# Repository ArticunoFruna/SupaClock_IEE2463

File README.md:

# SupaClock — Contexto y Guía del Proyecto

SupaClock es un sistema de salud inteligente usable (*wearable*) de pulsera desarrollado como parte del curso IEE2463. Su propósito es capturar biometría crítica en tiempo real, procesarla tanto en el dispositivo mediante técnicas de Inteligencia Artificial en el borde (TinyML), enviarla vía Bluetooth Low Energy (BLE) a una aplicación móvil de compañía y respaldarla de forma segura en la nube.

Este documento consolida el contexto general, características, funcionamiento de los sensores, arquitectura técnica y la organización del código según las tareas de desarrollo del proyecto.

---

## 1. Características Principales

*   **Procesamiento Concurrente y Multitarea:** Implementado bajo **ESP-IDF** (entorno oficial de Espressif) corriendo sobre **FreeRTOS** en un microcontrolador **Seeed Studio XIAO ESP32-S3** (y soportando el módulo **ESP32-C3 SuperMini** para captura de datos). Esto permite dividir el firmware en tareas con prioridades asignadas (adquisición de alta prioridad, procesamiento de actividad, interfaz gráfica e hilos de comunicación BLE).
*   **TinyML (Human Activity Recognition - HAR) en el Borde:** Inferencia en tiempo real de actividades físicas (Reposo, Caminar, Correr) ejecutada directamente en el reloj con un modelo de red neuronal convolucional 1D (CNN 1D) optimizado e integrado en C puro (`har_cnn1d`), operando con un muestreo del acelerómetro a 50 Hz.
*   **Interfaz Gráfica Integrada:** Pantalla LCD a color manejada mediante la librería gráfica **LVGL v8.4**, con refresco optimizado utilizando el bus SPI y **DMA (Direct Memory Access)** para liberar ciclos de procesamiento de la CPU.
*   **Aplicación Móvil Multiplataforma (Flutter & Dart):** 
    *   **Vista de Usuario:** Tablero interactivo con métricas en tiempo real, historial médico local e inicio de mediciones puntuales (*spot-checks*).
    *   **Procesamiento de Señales Local:** Incorpora el algoritmo **Pan-Tompkins** directamente en Dart para la detección de picos QRS y análisis de variabilidad del ritmo cardíaco (HRV) a partir de lecturas de ECG sin necesidad de servidores.
    *   **Modo Clínico:** Umbrales biométricos personalizables con lógica de estabilidad temporal para evitar falsas alarmas que disparan notificaciones locales y registros en la base de datos.
    *   **Modo Desarrollador Oculto:** Desbloqueado presionando 7 veces la versión en la pantalla de Configuración, otorgando acceso a flujos crudos de señales (ECG/IMU), grabación local a CSV e interfaz de comandos directos.
*   **Almacenamiento Local-First y Nube Serverless:** Almacenamiento local mediante Hive y sincronización asíncrona hacia Google Firebase (**Firestore** para métricas y **Storage** para las grabaciones CSV de electrocardiogramas completos), minimizando costes de infraestructura al no depender de Cloud Functions.

---

## 2. Sensores y Método de Funcionamiento

El dispositivo integra múltiples sensores biométricos conectados al bus físico común del microcontrolador.

### Resumen de Sensores
1.  **BMI160 (IMU - Unidad de Medición Inercial):** Acelerómetro y giroscopio conectados a través del bus **I2C**. Captura movimientos a 50 Hz para el algoritmo del podómetro (conteo de pasos) y para alimentar el modelo HAR en el borde.
2.  **AD8232 (ECG - Electrocardiograma):** Sensor analógico de pulso cardíaco de un solo canal. Se lee mediante el **ADC** interno del ESP32 a una frecuencia de muestreo de 500 Hz. Permite la visualización de la onda del electrocardiograma y el cálculo de intervalos RR.
3.  **MAX30102 (Pulsioxímetro):** Sensor óptico de ritmo cardíaco y saturación de oxígeno en sangre (SpO₂). Se comunica por **I2C**.
4.  **MAX30205 (Termómetro Clínico):** Sensor de temperatura de alta precisión diseñado para monitorización corporal humana. Se comunica por **I2C**.
5.  **MAX17048 (Fuel Gauge - Medidor de Batería):** Monitorea el voltaje y estado de carga de la batería Li-Po a través del bus **I2C**.

### Interfaz Física y buses de Comunicación
*   **Bus I2C (Compartido):** Los sensores BMI160, MAX30102, MAX30205 y MAX17048 comparten las líneas SDA y SCL del microcontrolador. Cada uno se identifica por su dirección de hardware hexadecimal única. Para evitar conflictos entre tareas concurrentes que acceden a este bus, el firmware emplea **Mutexes** de exclusión mutua de FreeRTOS.
*   **Bus SPI (Dedicado):** La pantalla LCD **ST7789** utiliza el bus SPI a alta velocidad con DMA para transferir buffers completos de píxeles generados en memoria RAM por LVGL.

### Protocolo de Comunicación BLE
El reloj actúa como servidor GATT y expone cuatro características principales bajo el protocolo biométrico de SupaClock:

| Característica UUID | Dirección | Descripción / Estructura del Dato |
| :--- | :--- | :--- |
| **`0xFF01`** | Notificación | **Flujo IMU Crudo:** Envío continuo a 50 Hz de paquetes de 12 bytes (`int16 ax, ay, az, gx, gy, gz`). |
| **`0xFF02`** | Notificación | **Métricas Agregadas (TLV):** Paquetes estructurados que contienen un encabezado y registros *Type-Length-Value* de variables (Ritmo cardíaco, SpO₂, Temperatura, Pasos, Batería, Estado HAR). |
| **`0xFF03`** | Notificación | **Flujo ECG Crudo:** Envío a 500 Hz de paquetes de 20 bytes que empaquetan 10 muestras consecutivas de ECG (`int16`). |
| **`0xFF04`** | Escritura | **Consola de Comandos:** Envío de órdenes al reloj (`0x00` detiene ECG, `0x01` inicia ECG, `0x02` activa depuración HAR, `0x03` detiene depuración). |

El formato **TLV (Type-Length-Value)** de la característica `0xFF02` estructura la información de la siguiente manera:
*   **Cabecera:** `Timestamp (u32)` + `Modo Energía (u8)` + `Longitud Datos (u8)`.
*   **Tipos de Registro (Types):**
    *   `0x01`: Frecuencia Cardíaca (BPM y calidad de señal).
    *   `0x02`: Saturación de Oxígeno (SpO₂ y calidad de señal).
    *   `0x03`: Temperatura Corporal.
    *   `0x04`: Estado de la Batería.
    *   `0x05`: Conteo de Pasos.
    *   `0x08`: Estado de Actividad HAR Consolidado.

---

## 3. Estructura de Directorios y Tareas de Desarrollo

El código fuente del proyecto se encuentra estructurado en carpetas dedicadas según el área de ingeniería y desarrollo:

```
SupaClock_IEE2463/
├── app/                  # Aplicación móvil en Flutter (Frontend y lógica del teléfono)
├── src/                  # Entrypoint del firmware y pruebas en ESP-IDF
├── lib/                  # Librerías internas y drivers de hardware para PlatformIO
├── hardware/             # Esquemáticos y PCB (diseño electrónico en Eagle/Kicad)
├── mechanical/           # Modelado en 3D del chasis y botón del reloj (OpenSCAD/STL)
├── tools/                # Scripts de Python para entrenamiento, simulaciones y debug
├── data_ml/              # Base de datos local de acelerometría para entrenamiento HAR
├── docs/                 # Hojas de datos (Datasheets), especificaciones y entregables
├── pc_simulator/         # Simulador de la interfaz gráfica en PC
└── scripts/              # Herramientas auxiliares y de generación de recursos gráficos
```

### 📂 Distribución de Tareas y Directorios de Trabajo

#### 1. Tareas de Firmware (C y C++ sobre ESP-IDF / FreeRTOS)
*   **Directorio principal de código:** [src/](file:///home/jay-c/Desktop/SupaClock_IEE2463/src) y [lib/](file:///home/jay-c/Desktop/SupaClock_IEE2463/lib)
*   **Configuración del entorno:** [platformio.ini](file:///home/jay-c/Desktop/SupaClock_IEE2463/platformio.ini) define los parámetros de compilación y dependencias.
*   **Controladores de sensores:** Ubicados en `lib/` bajo los nombres de cada driver:
    *   `bmi160_driver/` (Acelerómetro/Giroscopio)
    *   `max30102_driver/` (Pulsioximetría)
    *   `max30205_driver/` (Temperatura)
    *   `max17048_driver/` (Batería)
    *   `ad8232_driver/` & `ad8232_c3_driver/` (Electrocardiografía)
*   **Motor Gráfico (LVGL) y UI del Reloj:** Se trabaja en [lib/supaclock_ui/](file:///home/jay-c/Desktop/SupaClock_IEE2463/lib/supaclock_ui), [lib/ui_theme/](file:///home/jay-c/Desktop/SupaClock_IEE2463/lib/ui_theme) y [lib/ui_fonts/](file:///home/jay-c/Desktop/SupaClock_IEE2463/lib/ui_fonts).
*   **TinyML (CNN 1D) e Inferencia:** La lógica de red neuronal se encuentra en [lib/har_cnn1d/](file:///home/jay-c/Desktop/SupaClock_IEE2463/lib/har_cnn1d).
*   **Infraestructura BLE:** Las definiciones del protocolo e hilos de transmisión están en [lib/ble_telemetry/](file:///home/jay-c/Desktop/SupaClock_IEE2463/lib/ble_telemetry).
*   **Pruebas de Componentes:** Código para validar hardware de forma aislada en [src/tests/](file:///home/jay-c/Desktop/SupaClock_IEE2463/src/tests) (por ejemplo, tests de pantalla, BLE, sensores específicos o algoritmos particulares).

#### 2. Tareas de Desarrollo Móvil (Flutter & Dart)
*   **Directorio de trabajo:** [app/](file:///home/jay-c/Desktop/SupaClock_IEE2463/app)
*   **Interfaz de Usuario:** Vistas e interfaces en [app/lib/screens/](file:///home/jay-c/Desktop/SupaClock_IEE2463/app/lib/screens) (dashboard, settings, spot-check, dev-mode).
*   **Persistencia Local y Backend (Firebase):** Configuración de bases de datos y sincronización en [app/lib/services/](file:///home/jay-c/Desktop/SupaClock_IEE2463/app/lib/services) (`firestore_service.dart`, `storage_service.dart`, `local_store.dart` usando Hive).
*   **Procesamiento de Señal (ECG) y BLE:** Algoritmo Pan-Tompkins en `app/lib/services/pan_tompkins.dart` y parseo de tramas de telemetría en `app/lib/services/ble_service.dart`.
*   **Modelos de Datos:** Declarados en [app/lib/models/](file:///home/jay-c/Desktop/SupaClock_IEE2463/app/lib/models) para asegurar concordancia con Firebase.

#### 3. Tareas de Machine Learning y Análisis Científico (Python)
*   **Entrenamiento y Reentrenamiento HAR:** Los scripts para construir el modelo de actividad física se encuentran en [tools/train_har_cnn.py](file:///home/jay-c/Desktop/SupaClock_IEE2463/tools/train_har_cnn.py) y [tools/train_har_cnn_c3.py](file:///home/jay-c/Desktop/SupaClock_IEE2463/tools/train_har_cnn_c3.py).
*   **Recopilación de Datasets:** El historial de datasets recopilados clasificados para entrenar el clasificador se trabaja en [data_ml/](file:///home/jay-c/Desktop/SupaClock_IEE2463/data_ml) (ej. resting, walking, running, stairs).
*   **Reproducción y Debug del Modelo (Replay):** Script [tools/har_replay.py](file:///home/jay-c/Desktop/SupaClock_IEE2463/tools/har_replay.py) corre el modelo `.tflite` sobre logs de acelerometría y simula los filtros de suavizado.
*   **Calibración y Simulación de Umbrales:** `tools/calibrate_steps.py` (conteo de pasos) y `tools/debug_pt.py` (simulador Pan-Tompkins).
*   **Monitoreo del Hardware:** [tools/supaclock_monitor.py](file:///home/jay-c/Desktop/SupaClock_IEE2463/tools/supaclock_monitor.py) es una aplicación de escritorio para graficar ondas IMU/ECG y enviar comandos por puerto serie/BLE.

#### 4. Tareas de Diseño de Hardware (Electrónica / PCB)
*   **Directorio de trabajo:** [hardware/](file:///home/jay-c/Desktop/SupaClock_IEE2463/hardware)
*   Contiene los esquemáticos y placas (`.sch` y `.brd`) para el circuito portador del reloj, el módulo ECG AD8232 y el módulo medidor de batería, además de scripts de soporte de conexión como `build_v4_schematics.py` o `dump_nets.py`.

#### 5. Tareas de Diseño Mecánico (Carcasa y Botones)
*   **Directorio de trabajo:** [mechanical/](file:///home/jay-c/Desktop/SupaClock_IEE2463/mechanical)
*   Lugar donde se diseñan las cubiertas (superior, inferior y botones) en OpenSCAD (`.scad`) y se exportan a STL para manufactura mediante impresión 3D (`mechanical/stl/`, `mechanical/stl_v3/`).

#### 6. Tareas de Documentación del Proyecto
*   **Directorio de trabajo:** [docs/](file:///home/jay-c/Desktop/SupaClock_IEE2463/docs)
*   Incluye los manuales de arquitectura y conceptos (`docs/arquitectura_conceptos.md`), guías para nuevos desarrolladores (`docs/guia_introductoria.md`), protocolos de comunicación (`docs/ble_har_protocol.md`), resúmenes de avances e informes para las evaluaciones académicas del curso (`docs/Entrega1` a `docs/Entrega4`).

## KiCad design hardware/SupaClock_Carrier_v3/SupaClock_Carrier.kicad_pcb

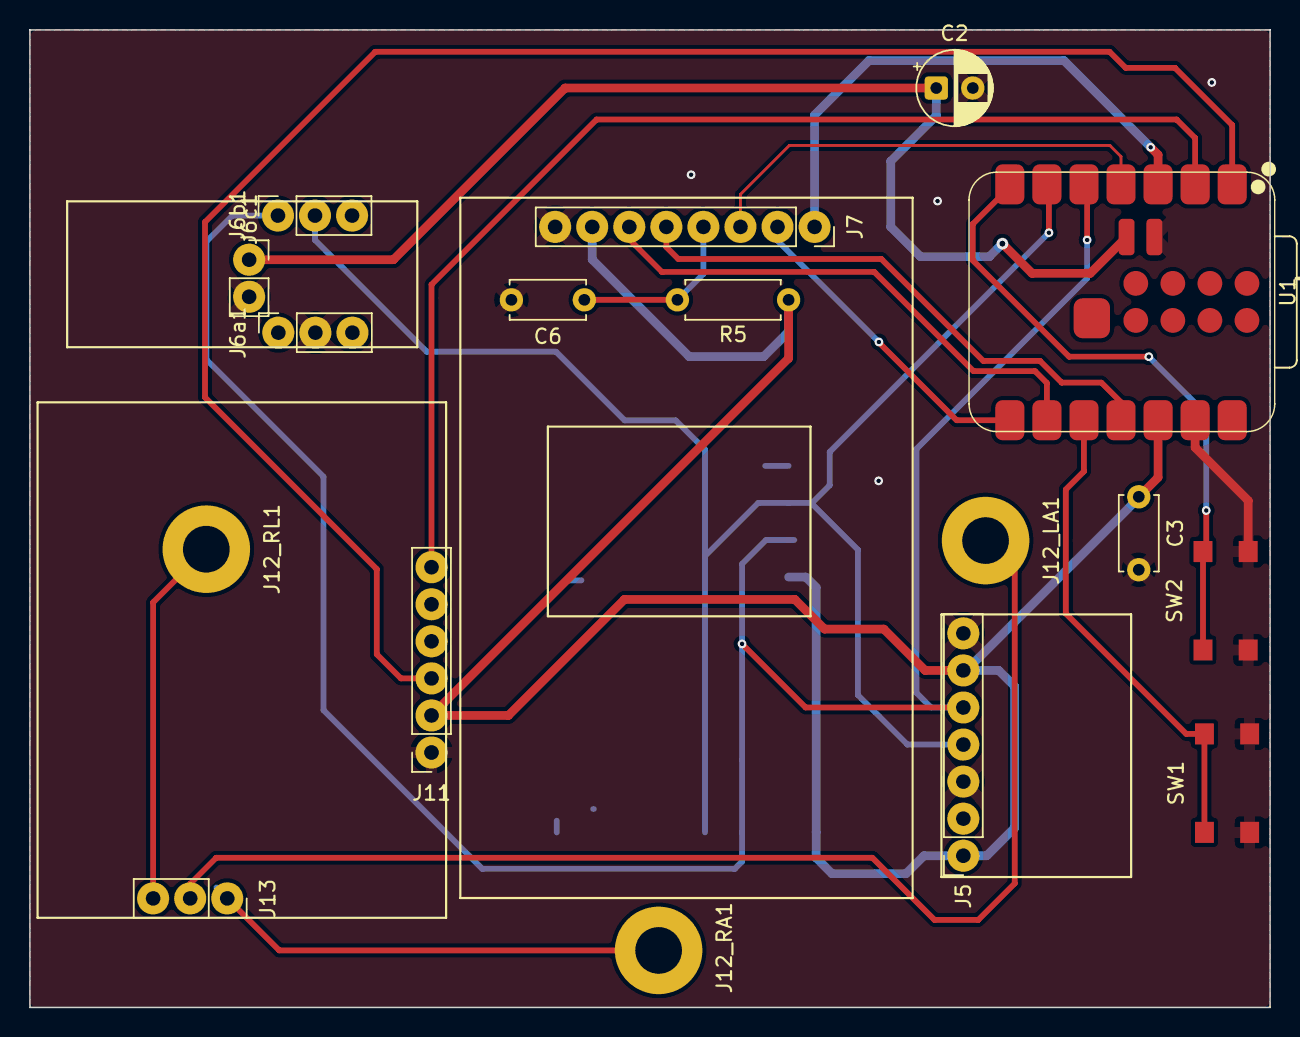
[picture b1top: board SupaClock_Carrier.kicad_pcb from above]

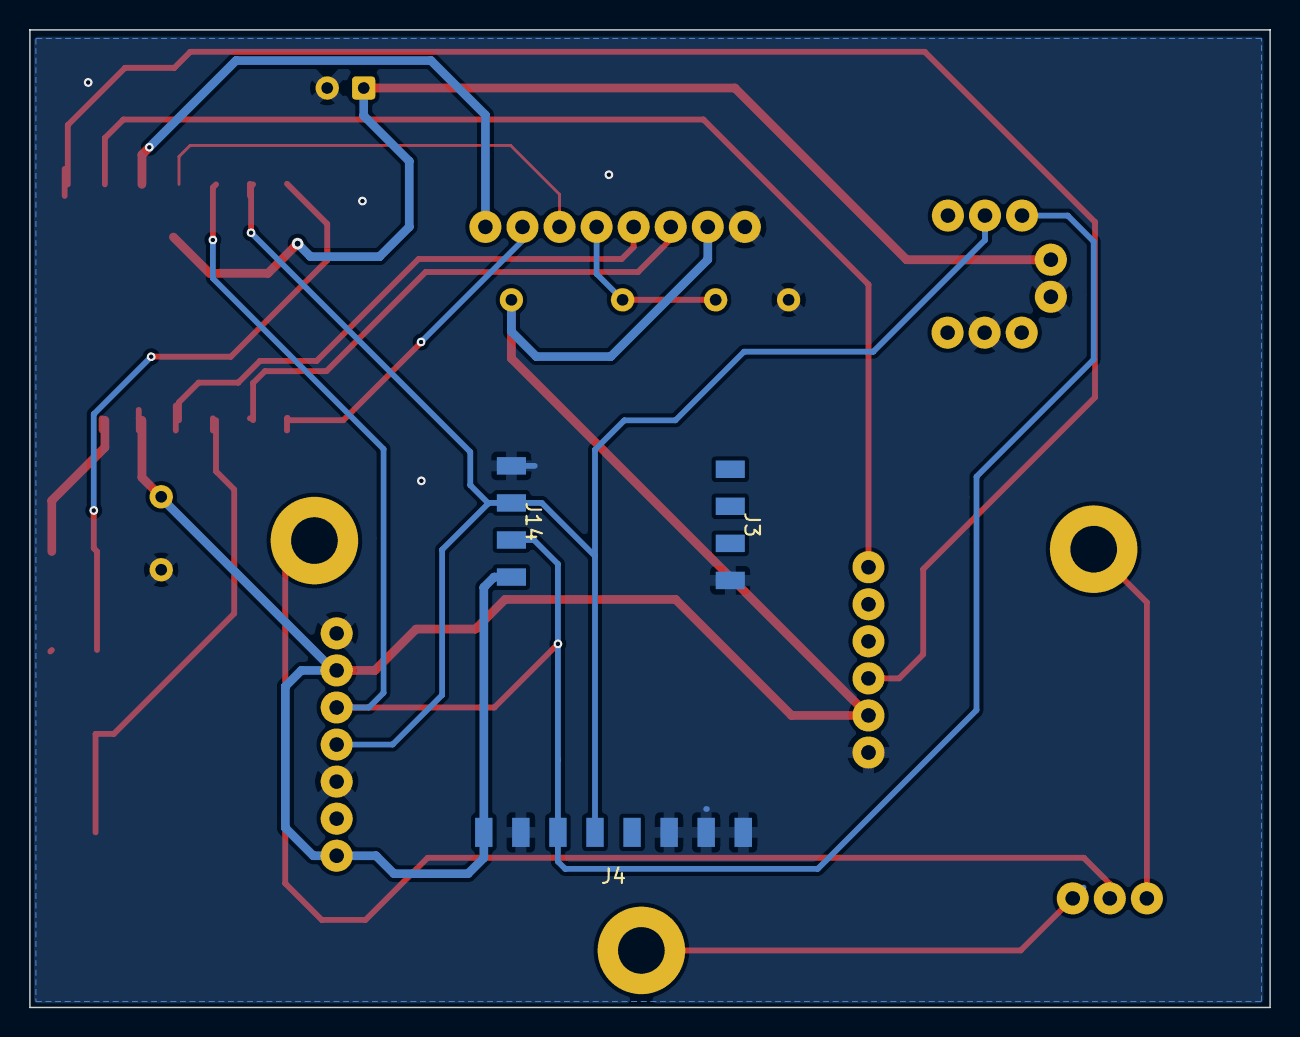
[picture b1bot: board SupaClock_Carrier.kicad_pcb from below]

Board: 2 copper layers, 85.0 x 67.0 mm, 20 parts (3 on the bottom side), 18 nets.

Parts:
C2: 10uF; CP_Radial_D5.0mm_P2.50mm
C3, C6: 100nF; C_Disc_D5.0mm_W2.5mm_P5.00mm
J3: MAX30102_top; MAX30102_Castellated_1x4
J4: MAX30205_8pad; MAX30205_8pad_Flush
J5: BMI160_7p; PinSocket_1x07_P2.54mm_Vertical
J6a1: MAX17048_L; PinSocket_1x03_P2.54mm_Vertical
J6b1: MAX17048_R; PinSocket_1x03_P2.54mm_Vertical
J6c1: MAX17048_BAT; PinSocket_1x02_P2.54mm_Vertical
J7: ST7789_1.69in; PinSocket_1x08_P2.54mm_Vertical
J11: AD8232_SparkFun; PinSocket_1x06_P2.54mm_Vertical
J12_LA1: ECG_LA_pad_M3; M3_Electrode_Pad
J12_RA1: ECG_RA_pad_M3; M3_Electrode_Pad
J12_RL1: ECG_RL_pad_M3; M3_Electrode_Pad
J13: AD8232_Pads_RA_LA_RL; PinSocket_1x03_P2.54mm_Vertical
J14: MAX30102_bot; MAX30102_Castellated_1x4
R5: 10k; R_Axial_DIN0207_L6.3mm_D2.5mm_P7.62mm_Horizontal
SW1: SELECT; SW_Tactile_Side_3.5x7.8mm
SW2: NEXT; SW_Tactile_Side_3.5x7.8mm
U1: XIAO-ESP32-S3; XIAO-ESP32-S3-SMD

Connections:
/+3V3: C3.1, J4.1, J5.1, J5.6, J7.7, J11.2, J14.1, R5.1, U1.12 (3V3)
/+BATT: C2.1, J6c1.1, U1.32 (BAT)
/BLK_PWM: J7.1, U1.3 (GPIO3_A2_D2)
/BTN_NEXT: SW2.1, U1.7 (GPIO43_D6_TX)
/BTN_SELECT: SW1.1, U1.10 (GPIO8_A9_D9_MISO)
/ECG_LA: J12_LA1.1 (Pin_1_1), J13.2
/ECG_OUT: J11.3, U1.1 (GPIO1_A0_D0)
/ECG_RA: J12_RA1.1 (Pin_1_1), J13.1
/ECG_RL: J12_RL1.1 (Pin_1_1), J13.3
/ECG_SDN: J11.6, U1.2 (GPIO2_A1_D1)
/GND: C2.2, C3.2, C6.2, J3.1 (Pin_1_1), J4.2, J4.6, J4.7, J4.8, J5.3, J5.7, J6a1.2 (Pin_2_2), J6c1.2, J7.8, J11.1, J14.4, SW1.2, SW2.2, U1.13 (GND), U1.33 (GND)
/I2C_SCL: J4.4, J5.4, J6b1.2, J14.3, U1.6 (GPIO6_A5_D5_SCL)
/I2C_SDA: J4.3, J5.5, J6b1.1, J14.2, U1.5 (GPIO5_A4_D4_SDA)
/SPI_CS: J7.2, U1.8 (GPIO44_D7_RX)
/SPI_DC: J7.3, U1.4 (GPIO4_A3_D3)
/SPI_MOSI: J7.5, U1.11 (GPIO9_A10_D10_MOSI)
/SPI_RES: C6.1, J7.4, R5.2
/SPI_SCK: J7.6, U1.9 (GPIO7_A8_D8_SCK)

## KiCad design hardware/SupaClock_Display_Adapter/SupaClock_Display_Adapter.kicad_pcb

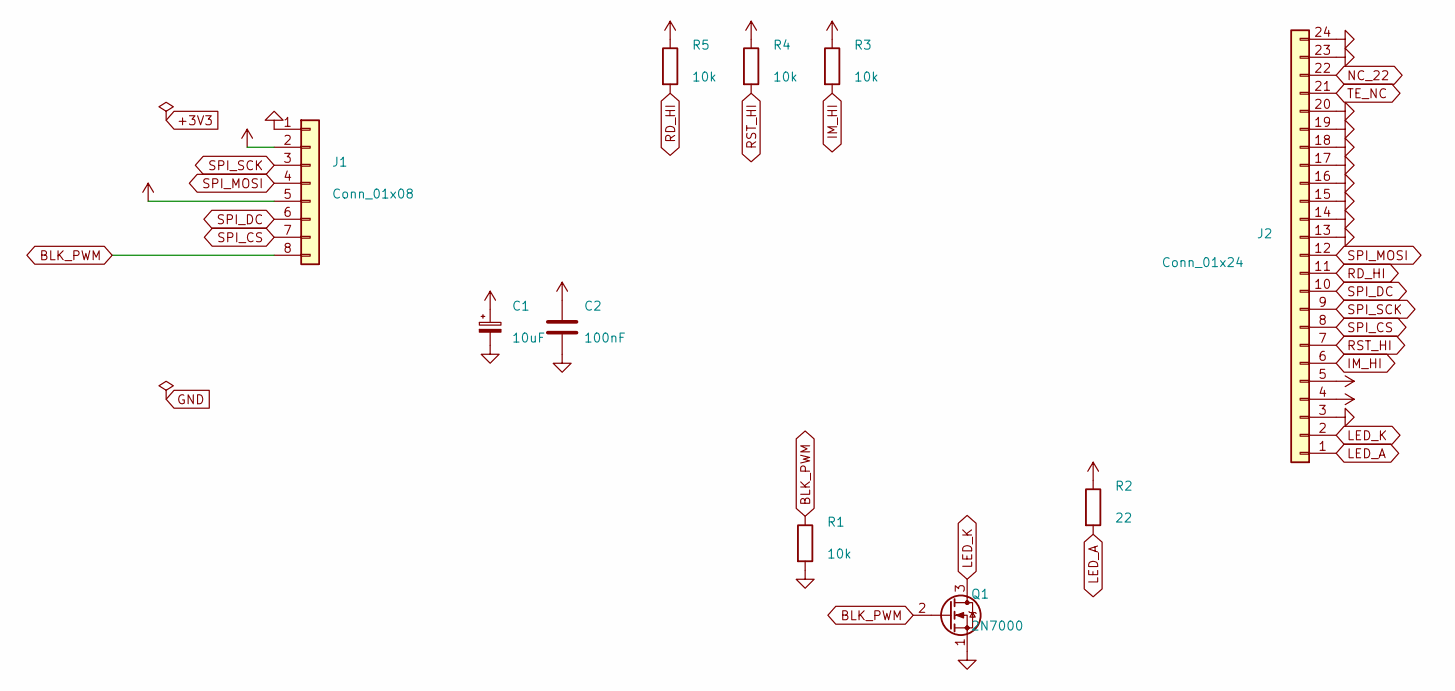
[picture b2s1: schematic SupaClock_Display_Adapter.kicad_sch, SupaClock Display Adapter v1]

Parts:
C1: 10uF; CP_Radial_D5.0mm_P2.50mm
C2: 100nF; C_Disc_D3.0mm_W1.6mm_P2.50mm
J1: Conn_01x08; PinHeader_1x08_P2.54mm_Vertical
J2: Conn_01x24; Hirose_FH12-24S-0.5SH_1x24-1MP_P0.50mm_Horizontal
Q1: 2N7000; TO-92_Inline
R1, R3, R4, R5: 10k; R_Axial_DIN0207_L6.3mm_D2.5mm_P10.16mm_Horizontal
R2: 22; R_Axial_DIN0207_L6.3mm_D2.5mm_P10.16mm_Horizontal

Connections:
+3V3: C1.1, C2.1, J1.2, J1.5, J2.4, J2.5, R2.1, R3.1, R4.1, R5.1
BLK_PWM: J1.8, Q1.2 (G), R1.1
GND: C1.2, C2.2, J1.1, J2.3, J2.13, J2.14, J2.15, J2.16, J2.17, J2.18, J2.19, J2.20, J2.23, J2.24, Q1.1 (S), R1.2
IM_HI: J2.6, R3.2
LED_A: J2.1, R2.2
LED_K: J2.2, Q1.3 (D)
NC_22: J2.22
RD_HI: J2.11, R5.2
RST_HI: J2.7, R4.2
SPI_CS: J1.7, J2.8
SPI_DC: J1.6, J2.10
SPI_MOSI: J1.4, J2.12
SPI_SCK: J1.3, J2.9
TE_NC: J2.21

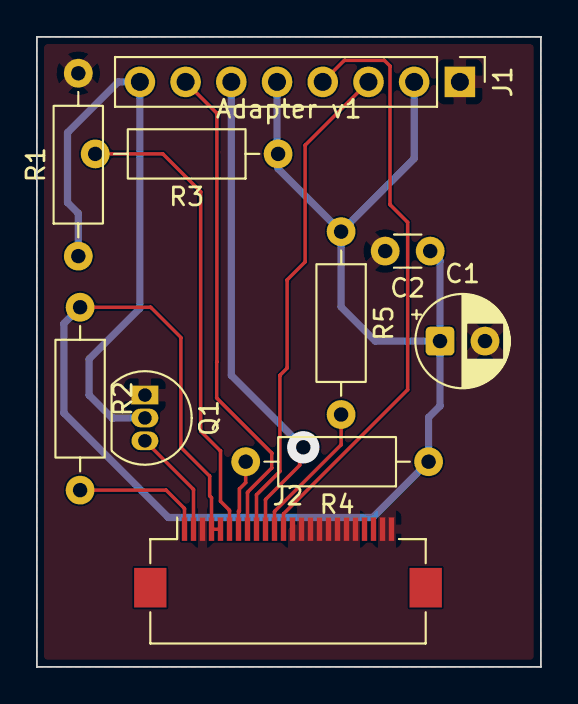
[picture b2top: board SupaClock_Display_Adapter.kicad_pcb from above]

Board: 2 copper layers, 28.0 x 35.0 mm, 10 parts (0 on the bottom side), 12 nets.

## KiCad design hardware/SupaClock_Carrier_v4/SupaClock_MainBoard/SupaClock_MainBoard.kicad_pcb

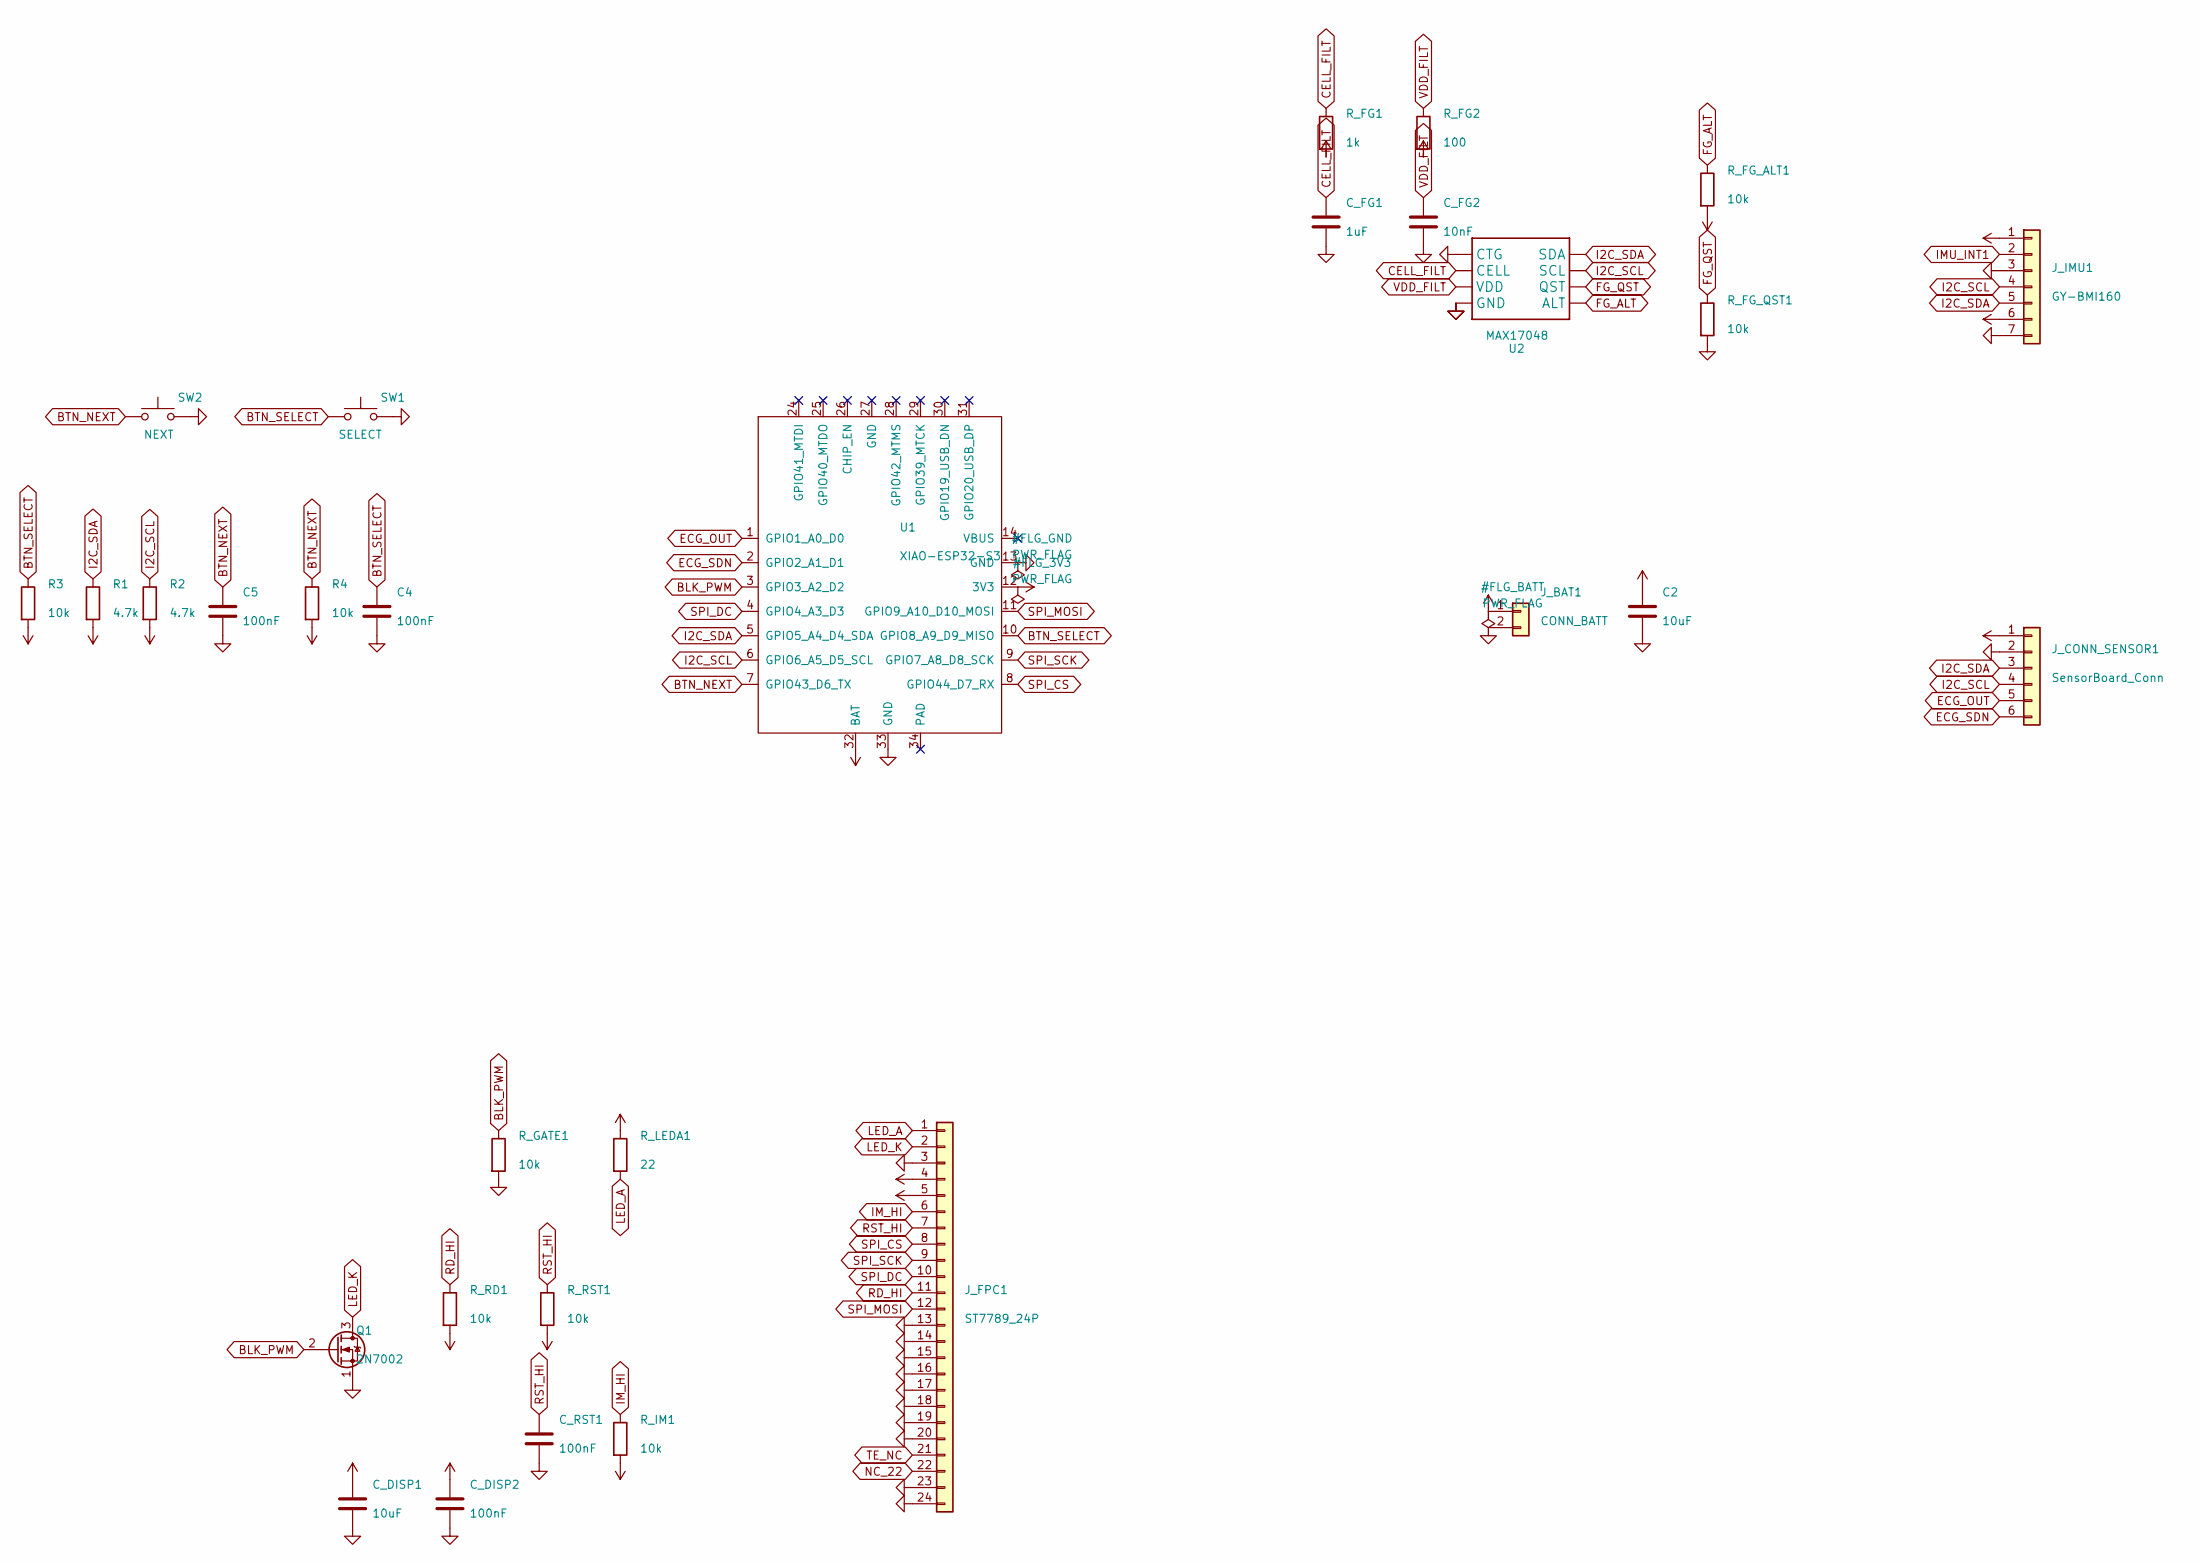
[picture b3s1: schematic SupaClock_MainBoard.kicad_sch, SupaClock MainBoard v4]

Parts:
C2: 10uF; C_0805_2012Metric_Pad1.18x1.45mm_HandSolder
C4, C5: 100nF; C_0805_2012Metric_Pad1.18x1.45mm_HandSolder
C_DISP1: 10uF; C_0805_2012Metric_Pad1.18x1.45mm_HandSolder
C_DISP2: 100nF; C_0805_2012Metric_Pad1.18x1.45mm_HandSolder
C_FG1: 1uF; C_0805_2012Metric_Pad1.18x1.45mm_HandSolder
C_FG2: 10nF; C_0805_2012Metric_Pad1.18x1.45mm_HandSolder
C_RST1: 100nF; C_0805_2012Metric_Pad1.18x1.45mm_HandSolder
J_BAT1: CONN_BATT; JST_PH_B2B-PH-K_1x02_P2.00mm_Vertical
J_CONN_SENSOR1: SensorBoard_Conn; JST_PH_B6B-PH-K_1x06_P2.00mm_Vertical
J_FPC1: ST7789_24P; Hirose_FH12-24S-0.5SH_1x24-1MP_P0.50mm_Horizontal
J_IMU1: GY-BMI160; PinHeader_1x07_P2.54mm_Vertical
Q1: 2N7002; SOT-23_Handsoldering
R1, R2: 4.7k; R_0805_2012Metric_Pad1.20x1.40mm_HandSolder
R3, R4: 10k; R_0805_2012Metric_Pad1.20x1.40mm_HandSolder
R_FG1: 1k; R_0805_2012Metric_Pad1.20x1.40mm_HandSolder
R_FG2: 100; R_0805_2012Metric_Pad1.20x1.40mm_HandSolder
R_FG_ALT1: 10k; R_0805_2012Metric_Pad1.20x1.40mm_HandSolder
R_FG_QST1: 10k; R_0805_2012Metric_Pad1.20x1.40mm_HandSolder
R_GATE1: 10k; R_0805_2012Metric_Pad1.20x1.40mm_HandSolder
R_IM1: 10k; R_0805_2012Metric_Pad1.20x1.40mm_HandSolder
R_LEDA1: 22; R_0805_2012Metric_Pad1.20x1.40mm_HandSolder
R_RD1: 10k; R_0805_2012Metric_Pad1.20x1.40mm_HandSolder
R_RST1: 10k; R_0805_2012Metric_Pad1.20x1.40mm_HandSolder
SW1: SELECT; SW_Tactile_Side_3.5x7.8mm
SW2: NEXT; SW_Tactile_Side_3.5x7.8mm
U1: XIAO-ESP32-S3; XIAO-ESP32-S3-SMD
U2: MAX17048; MAX17048_WDFN8_HandSolder

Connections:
+3V3: C_DISP1.1, C_DISP2.1, J_CONN_SENSOR1.1, J_FPC1.4, J_FPC1.5, J_IMU1.1, J_IMU1.6, R1.2, R2.2, R3.2, R4.2, R_FG_ALT1.2, R_IM1.2, R_LEDA1.1, R_RD1.2, R_RST1.2, U1.12 (3V3)
+BATT: C2.1, J_BAT1.1, R_FG1.2, R_FG2.2, U1.32 (BAT)
BLK_PWM: Q1.2 (G), R_GATE1.1, U1.3 (GPIO3_A2_D2)
BTN_NEXT: C5.1, R4.1, SW2.1, U1.7 (GPIO43_D6_TX)
BTN_SELECT: C4.1, R3.1, SW1.1, U1.10 (GPIO8_A9_D9_MISO)
CELL_FILT: C_FG1.1, R_FG1.1, U2.2 (CELL)
ECG_OUT: J_CONN_SENSOR1.5, U1.1 (GPIO1_A0_D0)
ECG_SDN: J_CONN_SENSOR1.6, U1.2 (GPIO2_A1_D1)
FG_ALT: R_FG_ALT1.1, U2.5 (ALT)
FG_QST: R_FG_QST1.1, U2.6 (QST)
GND: C2.2, C4.2, C5.2, C_DISP1.2, C_DISP2.2, C_FG1.2, C_FG2.2, C_RST1.2, J_BAT1.2, J_CONN_SENSOR1.2, J_FPC1.3, J_FPC1.13, J_FPC1.14, J_FPC1.15, J_FPC1.16, J_FPC1.17, J_FPC1.18, J_FPC1.19, J_FPC1.20, J_FPC1.23, J_FPC1.24, J_IMU1.3, J_IMU1.7, Q1.1 (S), R_FG_QST1.2, R_GATE1.2, SW1.2, SW2.2, U1.13 (GND), U1.33 (GND), U2.1 (CTG), U2.4 (GND), U2.EP (GND)
I2C_SCL: J_CONN_SENSOR1.4, J_IMU1.4, R2.1, U1.6 (GPIO6_A5_D5_SCL), U2.7 (SCL)
I2C_SDA: J_CONN_SENSOR1.3, J_IMU1.5, R1.1, U1.5 (GPIO5_A4_D4_SDA), U2.8 (SDA)
IMU_INT1: J_IMU1.2
IM_HI: J_FPC1.6, R_IM1.1
LED_A: J_FPC1.1, R_LEDA1.2
LED_K: J_FPC1.2, Q1.3 (D)
NC_22: J_FPC1.22
RD_HI: J_FPC1.11, R_RD1.1
RST_HI: C_RST1.1, J_FPC1.7, R_RST1.1
SPI_CS: J_FPC1.8, U1.8 (GPIO44_D7_RX)
SPI_DC: J_FPC1.10, U1.4 (GPIO4_A3_D3)
SPI_MOSI: J_FPC1.12, U1.11 (GPIO9_A10_D10_MOSI)
SPI_SCK: J_FPC1.9, U1.9 (GPIO7_A8_D8_SCK)
TE_NC: J_FPC1.21
VDD_FILT: C_FG2.1, R_FG2.1, U2.3 (VDD)

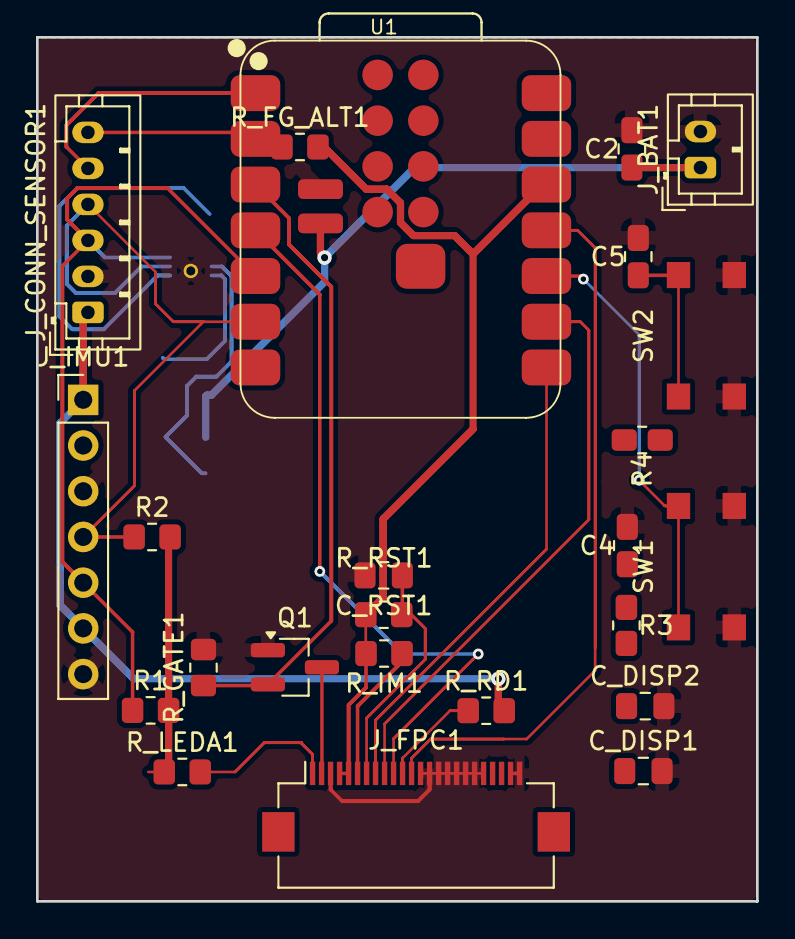
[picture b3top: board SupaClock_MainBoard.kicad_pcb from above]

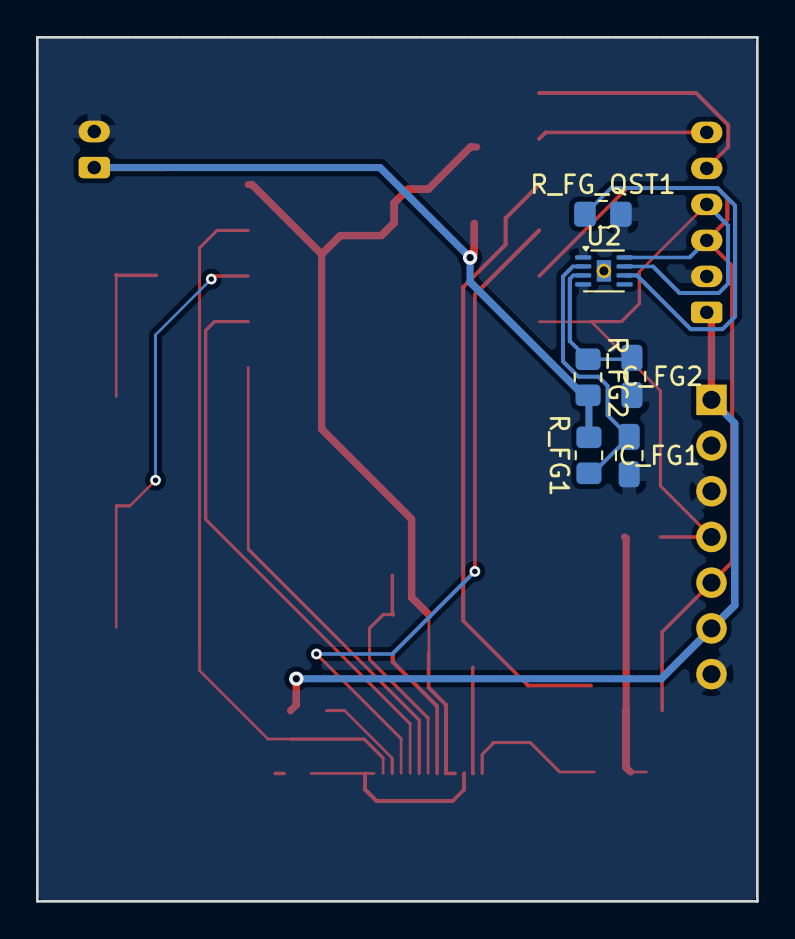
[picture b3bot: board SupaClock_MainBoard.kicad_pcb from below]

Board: 2 copper layers, 40.0 x 48.0 mm, 30 parts (6 on the bottom side), 23 nets.

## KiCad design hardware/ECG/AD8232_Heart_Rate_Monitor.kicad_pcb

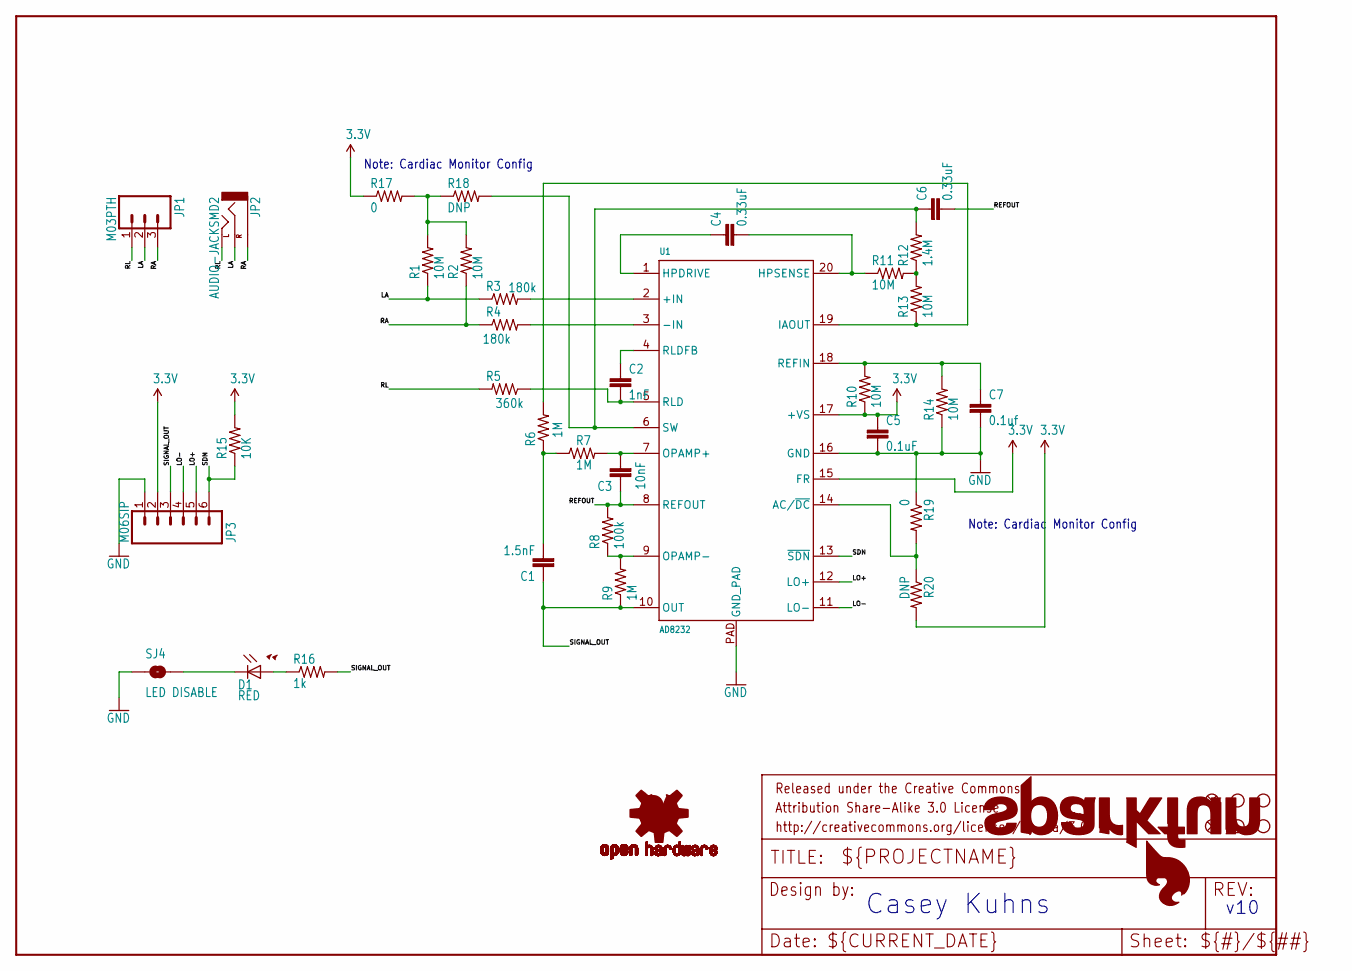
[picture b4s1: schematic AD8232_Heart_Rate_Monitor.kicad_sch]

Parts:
C1: 1.5nF; 0603-CAP
C2: 1nF; 0603-CAP
C3: 10nF; 0603-CAP
C4, C6: 0.33uF; 0805
C5: 0.1uF; 0603-CAP
C7: 0.1uf; 0603-CAP
D1: RED; LED-0603
FID1, FID2: FIDUCIAL1X2; FIDUCIAL-1X2
FRAME1: FRAME-LETTER; CREATIVE_COMMONS
JP1: M03PTH; 1X03
JP2: AUDIO-JACKSMD2; AUDIO-JACK-3.5MM-SMD
JP3: M06SIP; 1X06
LOGO1: OSHW-LOGOS; OSHW-LOGO-S
LOGO2: SFE_LOGO_NAME_FLAME.1_INCH; SFE_LOGO_NAME_FLAME_.1
R1, R2, R10, R11, R13, R14: 10M; 0603-RES
R3, R4: 180k; 0603-RES
R5: 360k; 0603-RES
R6, R7, R9: 1M; 0603-RES
R8: 100k; 0603-RES
R12: 1.4M; 0603-RES
R15: 10K; 0603-RES
R16: 1k; 0603-RES
R17, R19: 0; 0603
R18, R20: DNP; 0603
SJ4: LED DISABLE; SJ_2S-TRACE
STANDOFF1, STANDOFF2, STANDOFF3, STANDOFF4: STAND-OFF
U1: AD8232; LFCSP_20

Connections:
3.3V: C5.1, JP3.2, R10.1, R15.2, R17.1, R20.2, U1.15 (FR), U1.17 (+VS)
GND: C5.2, C7.2, JP3.1, R14.1, R19.1, SJ4.1, U1.16 (GND), U1.PAD (GND_PAD)
LA: JP1.2, JP2.RING (RIGHT), R1.1, R3.1
LO+: JP3.5, U1.12 (LO+)
LO-: JP3.4, U1.11 (LO-)
unnamed: R3.2, U1.2 (+IN)
unnamed: R4.2, U1.3 (-IN)
unnamed: C3.2, R7.2, U1.7 (OPAMP+)
unnamed: C4.2, R11.1, U1.20 (HPSENSE)
unnamed: C7.1, R10.2, R14.2, U1.18 (REFIN)
unnamed: D1.A, R16.1
unnamed: R8.1, R9.2, U1.9 (OPAMP-)
unnamed: R6.2, R13.1, U1.19 (IAOUT)
unnamed: C1.2, R6.1, R7.1
unnamed: D1.C, SJ4.2
unnamed: R19.2, R20.1, U1.14 (AC/~DC)
unnamed: C4.1, U1.1 (HPDRIVE)
unnamed: R11.2, R12.1, R13.2
unnamed: C6.1, R12.2, R18.2, U1.6 (SW)
unnamed: C2.1, U1.4 (RLDFB)
unnamed: C2.2, R5.1, U1.5 (RLD)
unnamed: R1.2, R2.2, R17.2, R18.1
RA: JP1.3, JP2.SLEEVE, R2.1, R4.1
REFOUT: C3.1, C6.2, R8.2, U1.8 (REFOUT)
RL: JP1.1, JP2.TIP (LEFT), R5.2
SDN: JP3.6, R15.1, U1.13 (~SDN)
SIGNAL_OUT: C1.1, JP3.3, R9.1, R16.2, U1.10 (OUT)

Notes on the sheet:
Note: Cardiac Monitor Config
v10
Casey Kuhns

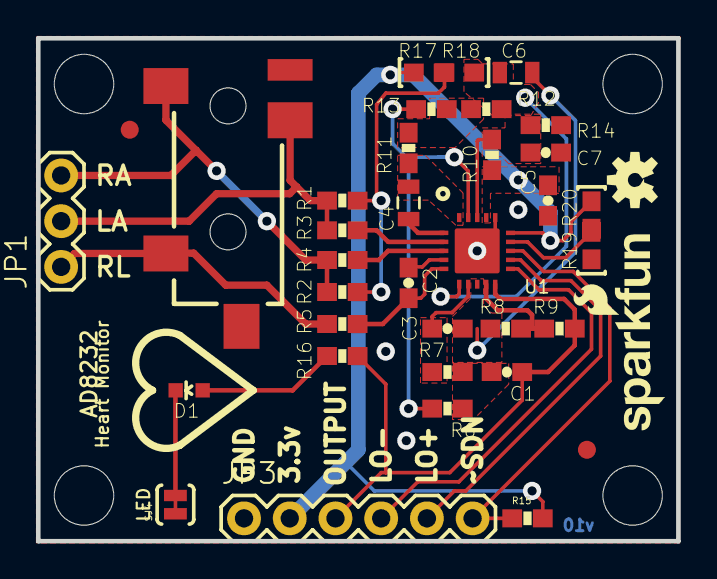
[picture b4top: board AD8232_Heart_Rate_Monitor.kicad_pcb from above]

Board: 2 copper layers, 35.6 x 27.9 mm, 42 parts (0 on the bottom side), 27 nets.

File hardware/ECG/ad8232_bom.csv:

"Reference","Value","Footprint"
"C1","1.5nF","AD8232_Heart_Rate_Monitor:0603-CAP"
"C2","1nF","AD8232_Heart_Rate_Monitor:0603-CAP"
"C3","10nF","AD8232_Heart_Rate_Monitor:0603-CAP"
"C4","0.33uF","AD8232_Heart_Rate_Monitor:0805"
"C5","0.1uF","AD8232_Heart_Rate_Monitor:0603-CAP"
"C6","0.33uF","AD8232_Heart_Rate_Monitor:0805"
"C7","0.1uf","AD8232_Heart_Rate_Monitor:0603-CAP"
"D1","RED","AD8232_Heart_Rate_Monitor:LED-0603"
"FID1","FIDUCIAL1X2","AD8232_Heart_Rate_Monitor:FIDUCIAL-1X2"
"FID2","FIDUCIAL1X2","AD8232_Heart_Rate_Monitor:FIDUCIAL-1X2"
"FRAME1","FRAME-LETTER","AD8232_Heart_Rate_Monitor:CREATIVE_COMMONS"
"JP1","M03PTH","AD8232_Heart_Rate_Monitor:1X03"
"JP2","AUDIO-JACKSMD2","AD8232_Heart_Rate_Monitor:AUDIO-JACK-3.5MM-SMD"
"JP3","M06SIP","AD8232_Heart_Rate_Monitor:1X06"
"LOGO1","OSHW-LOGOS","AD8232_Heart_Rate_Monitor:OSHW-LOGO-S"
"LOGO2","SFE_LOGO_NAME_FLAME.1_INCH","AD8232_Heart_Rate_Monitor:SFE_LOGO_NAME_FLAME_.1"
"R1","10M","AD8232_Heart_Rate_Monitor:0603-RES"
"R2","10M","AD8232_Heart_Rate_Monitor:0603-RES"
"R3","180k","AD8232_Heart_Rate_Monitor:0603-RES"
"R4","180k","AD8232_Heart_Rate_Monitor:0603-RES"
"R5","360k","AD8232_Heart_Rate_Monitor:0603-RES"
"R6","1M","AD8232_Heart_Rate_Monitor:0603-RES"
"R7","1M","AD8232_Heart_Rate_Monitor:0603-RES"
"R8","100k","AD8232_Heart_Rate_Monitor:0603-RES"
"R9","1M","AD8232_Heart_Rate_Monitor:0603-RES"
"R10","10M","AD8232_Heart_Rate_Monitor:0603-RES"
"R11","10M","AD8232_Heart_Rate_Monitor:0603-RES"
"R12","1.4M","AD8232_Heart_Rate_Monitor:0603-RES"
"R13","10M","AD8232_Heart_Rate_Monitor:0603-RES"
"R14","10M","AD8232_Heart_Rate_Monitor:0603-RES"
"R15","10K","AD8232_Heart_Rate_Monitor:0603-RES"
"R16","1k","AD8232_Heart_Rate_Monitor:0603-RES"
"R17","0","AD8232_Heart_Rate_Monitor:0603"
"R18","DNP","AD8232_Heart_Rate_Monitor:0603"
"R19","0","AD8232_Heart_Rate_Monitor:0603"
"R20","DNP","AD8232_Heart_Rate_Monitor:0603"
"SJ4","LED DISABLE","AD8232_Heart_Rate_Monitor:SJ_2S-TRACE"
"STANDOFF1","STAND-OFF","AD8232_Heart_Rate_Monitor:STAND-OFF"
"STANDOFF2","STAND-OFF","AD8232_Heart_Rate_Monitor:STAND-OFF"
"STANDOFF3","STAND-OFF","AD8232_Heart_Rate_Monitor:STAND-OFF"
"STANDOFF4","STAND-OFF","AD8232_Heart_Rate_Monitor:STAND-OFF"
"U1","AD8232","AD8232_Heart_Rate_Monitor:LFCSP_20"

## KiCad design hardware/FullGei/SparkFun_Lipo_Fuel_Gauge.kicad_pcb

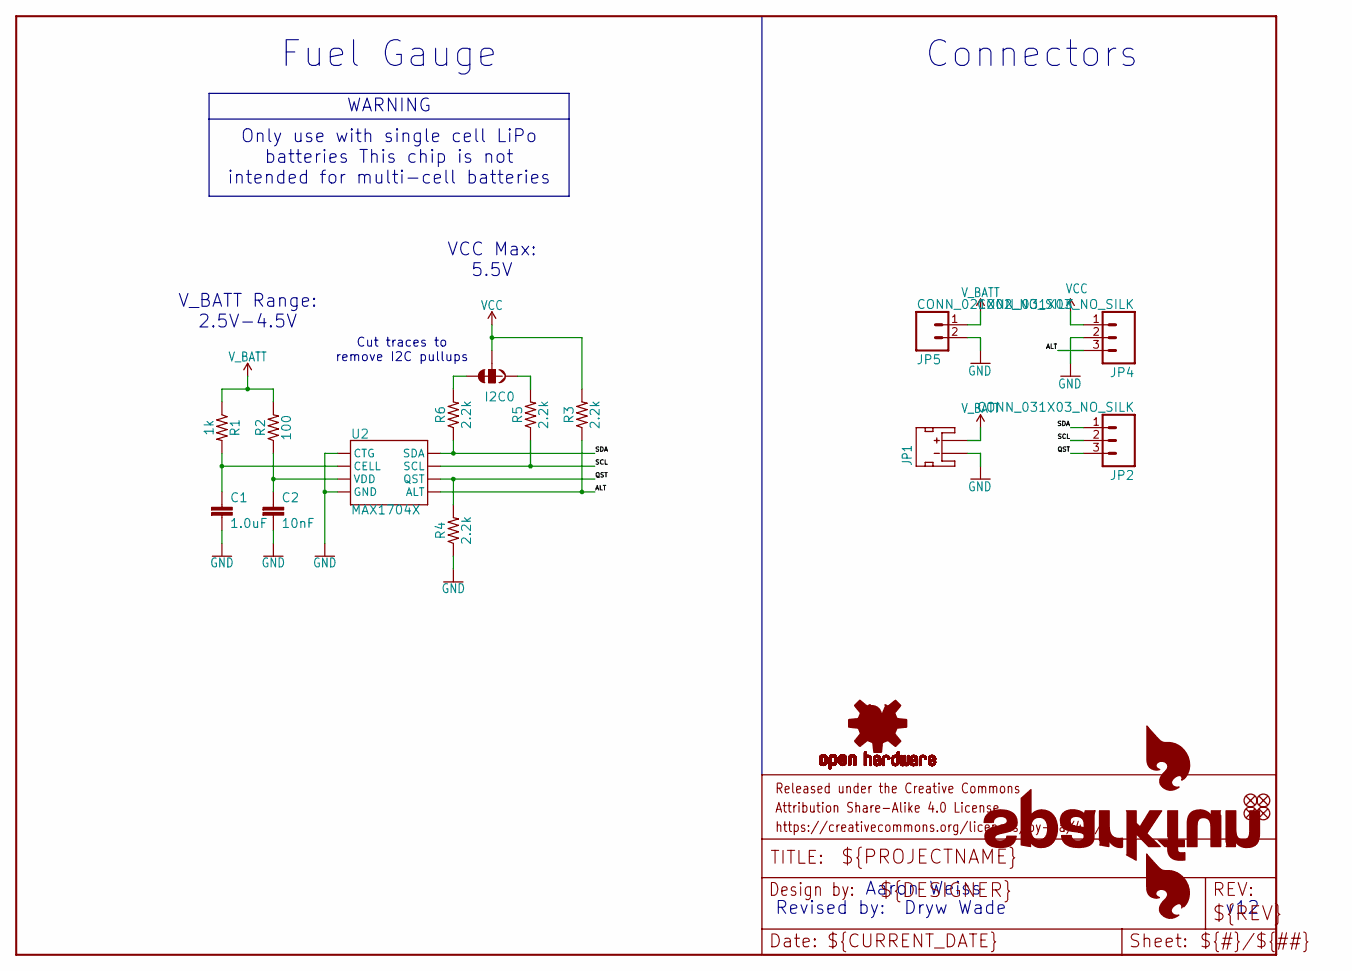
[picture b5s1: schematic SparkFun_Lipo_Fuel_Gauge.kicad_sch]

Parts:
C1: 1.0uF; 0402-TIGHT
C2: 10nF; 0402-TIGHT
FRAME1: FRAME-LETTER; CREATIVE_COMMONS
I2C0: JUMPER-SMT_3_2-NC_TRACE_SILK; SMT-JUMPER_3_2-NC_TRACE_SILK
JP1: input; JST-2-SMD
JP2, JP4: CONN_031X03_NO_SILK; 1X03_NO_SILK
JP3: SFE_LOGO_FLAME.1_INCH; SFE_LOGO_FLAME_.1
JP5: CONN_021X02_NO_SILK; 1X02_NO_SILK
JP6, JP7, JP8, JP9: FIDUCIALUFIDUCIAL; FIDUCIAL-MICRO
LOGO1: SFE_LOGO_NAME_FLAMEBLANK; BLANK
R1: 1k; 0402-TIGHT
R2: 100; 0402-TIGHT
R3, R4, R5, R6: 2.2k; 0402-TIGHT
U2: MAX1704X; TDFN-8
U$1: OSHW-LOGOS; OSHW-LOGO-S

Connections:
ALT: JP4.3, R3.1, U2.5 (ALT)
GND: C1.2, C2.2, JP1.1 (-), JP4.2, JP5.2, R4.1, U2.1 (CTG), U2.4 (GND), U2.EP (GND)
unnamed: I2C0.3, R6.2
unnamed: C1.1, R1.2, U2.2 (CELL)
unnamed: I2C0.1, R5.2
QST: JP2.3, R4.2, U2.6 (QST)
SCL: JP2.2, R5.1, U2.7 (SCL)
SDA: JP2.1, R6.1, U2.8 (SDA)
VCC: I2C0.2, JP4.1, R3.2
VDD: C2.1, R2.1, U2.3 (VDD)
V_BATT: JP1.2 (+), JP5.1, R1.1, R2.2

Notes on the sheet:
Aaron Weiss
Cut traces to remove I2C pullups
VCC Max: 5.5V
Dryw Wade
V_BATT Range: 2.5V-4.5V
Revised by:
Only use with single cell LiPo batteries~{} This chip is not intended for multi-cell batteries~{}
Connectors
Fuel Gauge
WARNING
v12

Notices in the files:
hardware/ECG/AD8232_Heart_Rate_Monitor.kicad_sch:
Released under the Creative Commons
http://creativecommons.org/licenses/by-sa/3.0
hardware/FullGei/SparkFun_Lipo_Fuel_Gauge.kicad_sch:
https://creativecommons.org/licenses/by-sa/4.0
parts and their libraries:
Released under the Creative Commons Attribution Share-Alike 3.0 License
Released under the Creative Commons Attribution Share-Alike 4.0 License
